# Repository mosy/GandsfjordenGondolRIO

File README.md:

# Gandsfjorden Gondol RIO
## 17.08.24 Skjema for RIO

## 07.08.24 V2 prototype ankommet

Feil etter IO-sjekk:
1 pinne 39/40 er ikke analog inngang, fikses ved av vi bare trenger 1 AI og en PT1000 inngang PT1000 Kobles mot AI2
2 Mangler elektrolytt kondensator, fungerer fint uten
3 hol til skruer er 3.0. settes til 3.1 i neste versjon. 

## 06.09.23

A simple Remote In Out training modeule to interface 24V industrial signals to a modbus PLC. 

 GandsfjordenGondolRIO

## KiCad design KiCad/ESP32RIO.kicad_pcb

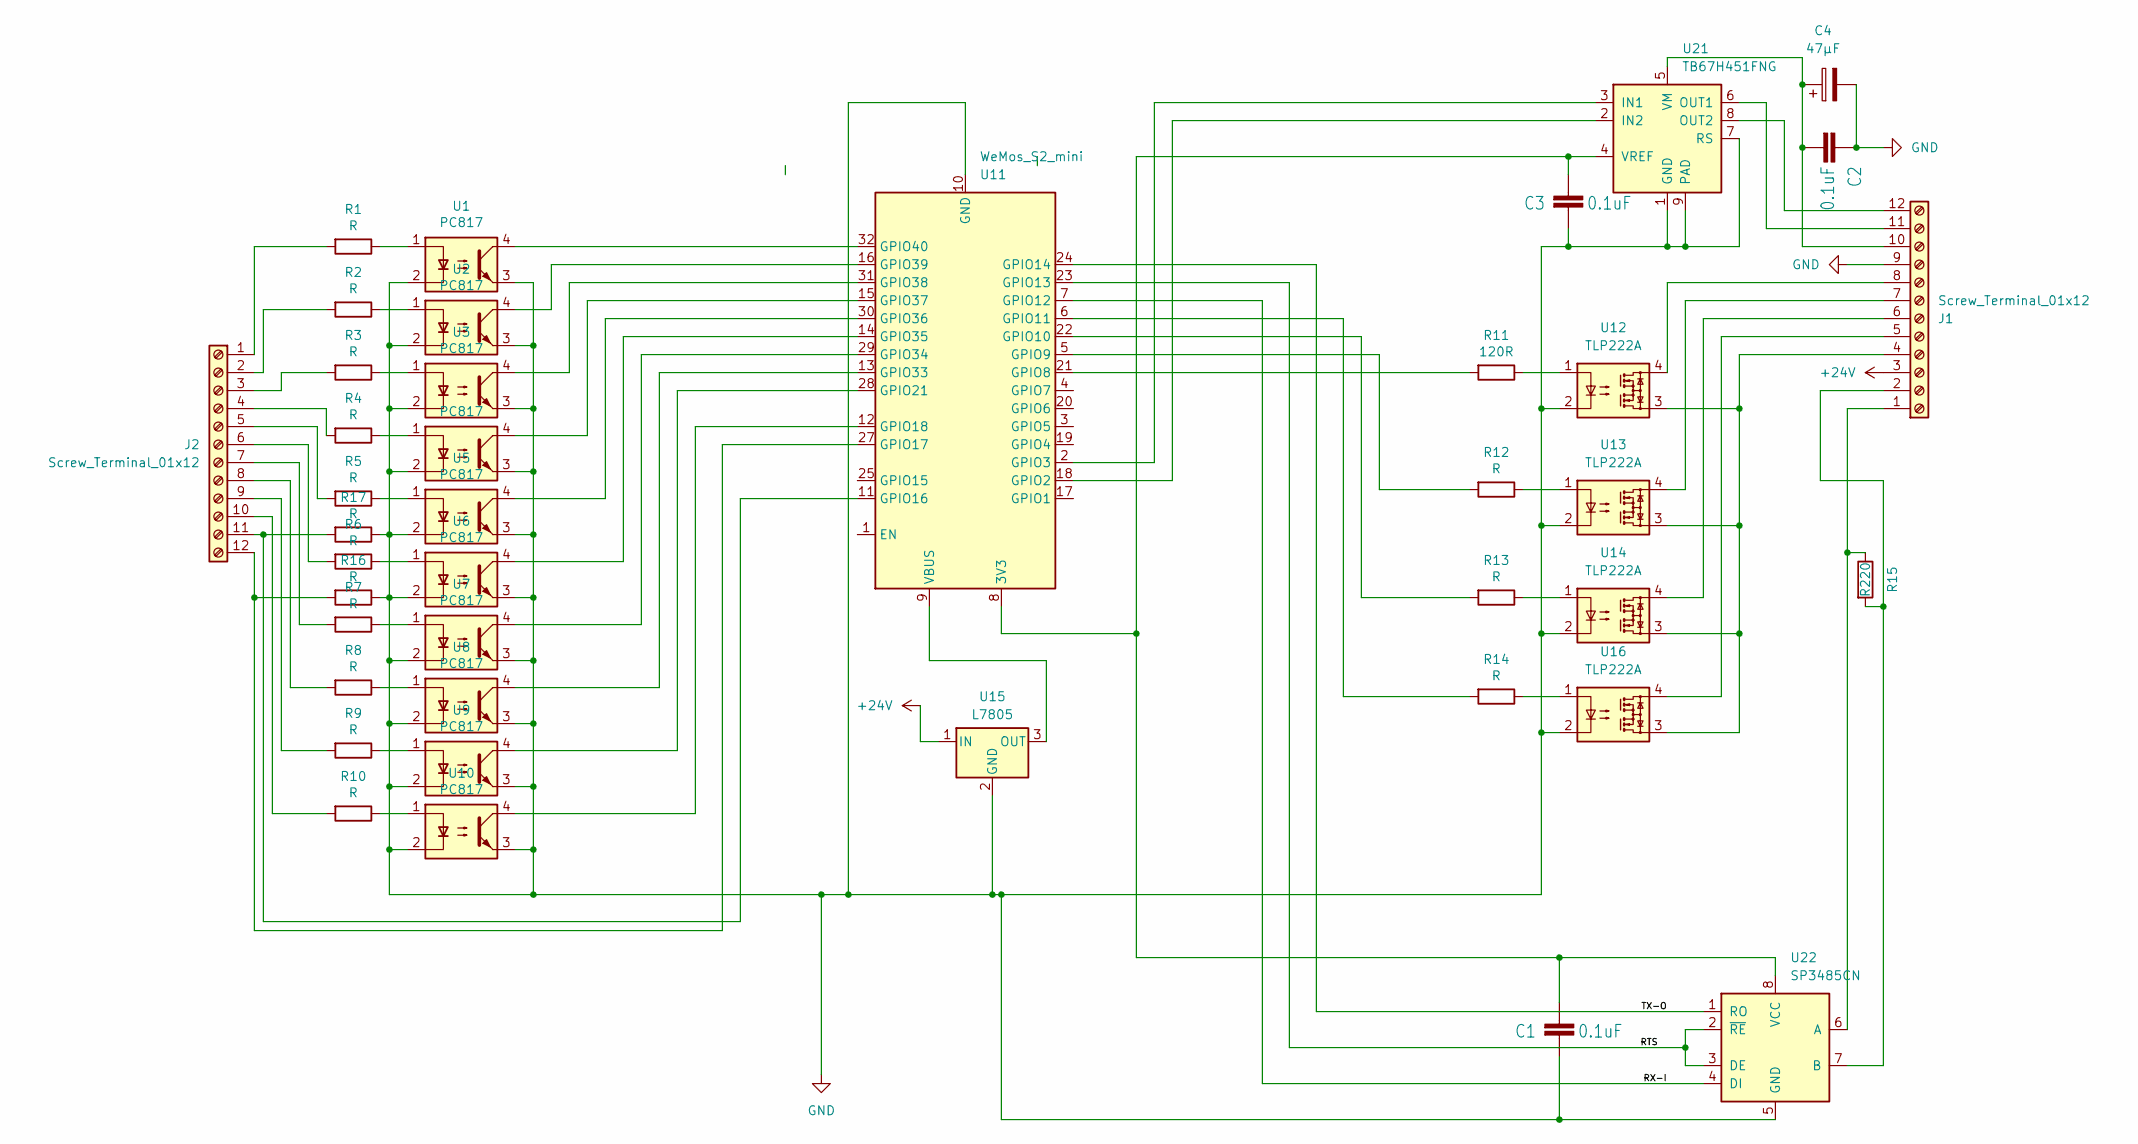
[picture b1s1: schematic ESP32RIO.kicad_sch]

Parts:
C1, C2, C3: 0.1uF; C_1206_3216Metric_Pad1.33x1.80mm_HandSolder
C4: 47µF; CP_Radial_D5.0mm_P2.50mm
J1, J2: Screw_Terminal_01x12; TerminalBlock_Phoenix_MKDS-1,5-12_1x12_P5.00mm_Horizontal
R1, R2, R3, R4, R5, R6, R7, R8, R9, R10, R12, R13, R14, R16, R17: R; R_Axial_DIN0204_L3.6mm_D1.6mm_P2.54mm_Vertical
R11: 120R; R_Axial_DIN0204_L3.6mm_D1.6mm_P2.54mm_Vertical
R15: R220; R_Axial_DIN0204_L3.6mm_D1.6mm_P2.54mm_Vertical
U1, U2, U3, U4, U5, U6, U7, U8, U9, U10: PC817; DIP-4_W7.62mm
U11: WeMos_S2_mini; WEMOS_S2_mini
U12, U13, U14, U16: TLP222A; DIP-4_W7.62mm
U15: L7805; TO-252-2
U21: TB67H451FNG; SOIC-8-1EP_3.9x4.9mm_P1.27mm_EP2.41x3.3mm
U22: SP3485CN; SOIC-8_3.9x4.9mm_P1.27mm

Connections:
+24V: J1.3, U15.1 (IN)
/RTS: U11.23 (GPIO13), U22.2 (~RE), U22.3 (DE)
/RX-I: U11.7 (GPIO12), U22.4 (DI)
/TX-O: U11.24 (GPIO14), U22.1 (RO)
GND: C1.2, C2.1, C3.2, C4.2, J1.9, R16.1, R17.1, U1.2, U1.3, U2.2, U2.3, U3.2, U3.3, U4.2, U4.3, U5.2, U5.3, U6.2, U6.3, U7.2, U7.3, U8.2, U8.3, U9.2, U9.3, U10.2, U10.3, U11.10 (GND), U11.26 (GND), U12.2, U13.2, U14.2, U15.2 (GND), U16.2, U21.1 (GND), U21.7 (RS), U21.9 (PAD), U22.5 (GND)
unnamed: J1.1, R15.1, U22.6 (A)
unnamed: J1.2, R15.2, U22.7 (B)
unnamed: J1.4, U12.3, U13.3, U14.3, U16.3
unnamed: J1.5, U16.4
unnamed: J1.6, U14.4
unnamed: J1.7, U13.4
unnamed: J1.8, U12.4
unnamed: C2.2, C4.1, J1.10, U21.5 (VM)
unnamed: J1.11, U21.6 (OUT1)
unnamed: J1.12, U21.8 (OUT2)
unnamed: J2.1, R1.2
unnamed: J2.2, R2.2
unnamed: J2.3, R3.2
unnamed: J2.4, R4.2
unnamed: J2.5, R5.2
unnamed: J2.6, R6.2
unnamed: J2.7, R7.2
unnamed: J2.8, R8.2
unnamed: J2.9, R9.2
unnamed: J2.10, R10.2
unnamed: J2.11, R17.2, U11.11 (GPIO16)
unnamed: J2.12, R16.2, U11.27 (GPIO17)
unnamed: R1.1, U1.1
unnamed: R2.1, U2.1
unnamed: R3.1, U3.1
unnamed: R4.1, U4.1
unnamed: R5.1, U5.1
unnamed: R6.1, U6.1
unnamed: R7.1, U7.1
unnamed: R8.1, U8.1
unnamed: R9.1, U9.1
unnamed: R10.1, U10.1
unnamed: R11.1, U12.1
unnamed: R12.1, U13.1
unnamed: R13.1, U14.1
unnamed: R14.1, U16.1
unnamed: C1.1, C3.1, U11.8 (3V3), U21.4 (VREF), U22.8 (VCC)
unnamed: U11.18 (GPIO2), U21.2 (IN2)
unnamed: U11.2 (GPIO3), U21.3 (IN1)
unnamed: R11.2, U11.21 (GPIO8)
unnamed: R12.2, U11.5 (GPIO9)
unnamed: R13.2, U11.22 (GPIO10)
unnamed: R14.2, U11.6 (GPIO11)
unnamed: U10.4, U11.12 (GPIO18)
unnamed: U9.4, U11.28 (GPIO21)
unnamed: U8.4, U11.13 (GPIO33)
unnamed: U7.4, U11.29 (GPIO34)
unnamed: U6.4, U11.14 (GPIO35)
unnamed: U5.4, U11.30 (GPIO36)
unnamed: U4.4, U11.15 (GPIO37)
unnamed: U3.4, U11.31 (GPIO38)
unnamed: U2.4, U11.16 (GPIO39)
unnamed: U1.4, U11.32 (GPIO40)
unnamed: U11.9 (VBUS), U15.3 (OUT)

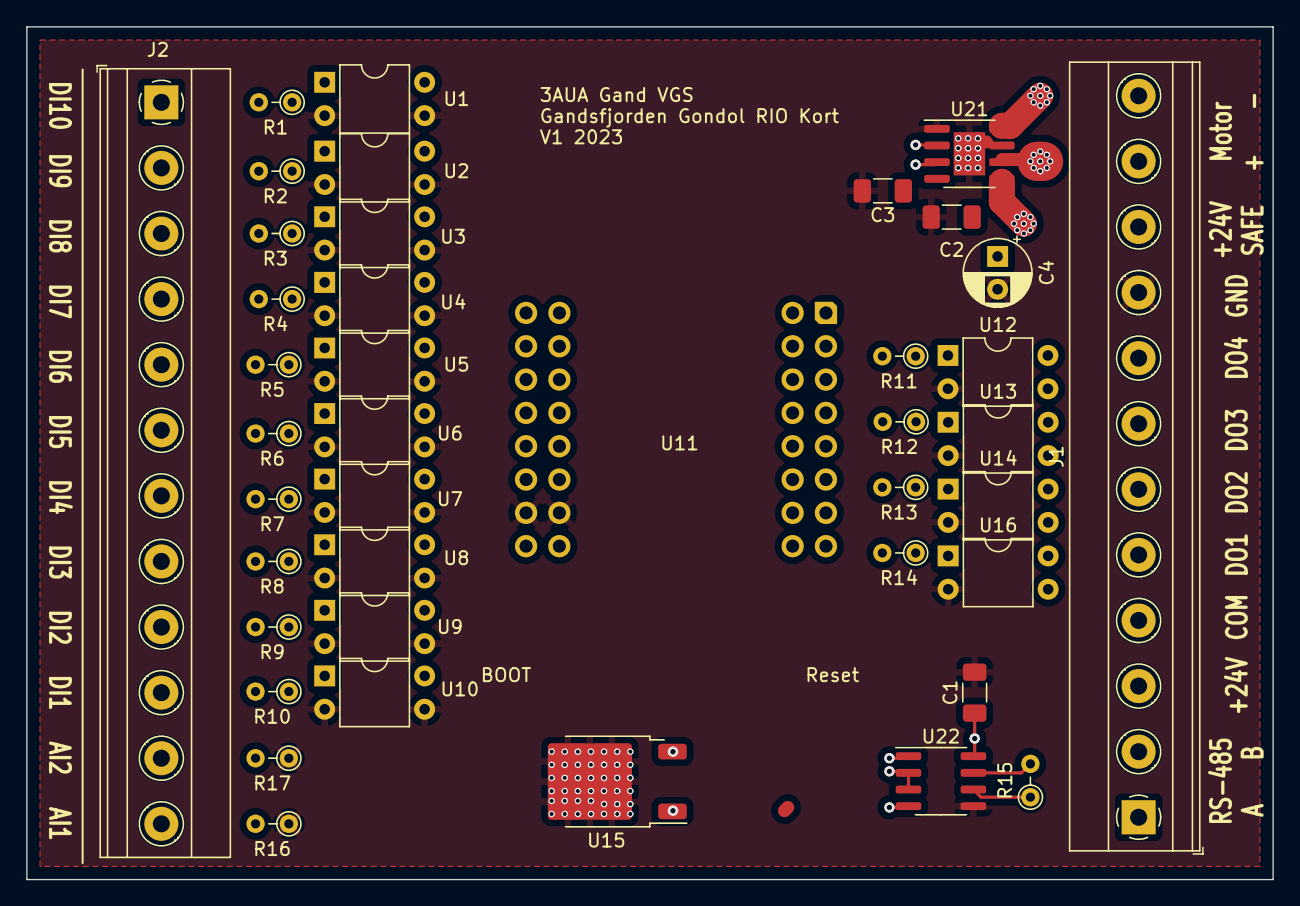
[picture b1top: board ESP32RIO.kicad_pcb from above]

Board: 4 copper layers, 95.0 x 65.0 mm, 41 parts (1 on the bottom side), 59 nets.

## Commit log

2023-03-11 Fungerende modbus med 8DI og 8DO
2023-03-11 Lagt til koblingstegning
2023-03-11 Lagt til koblingstegning svg
2023-03-14 Startet på skjema
2023-03-15 14DI og 2 AI virker
2023-03-15 lagt til bilder
2023-03-17 Lagt til utganger og funnet problemer med 4-20mA ut
2023-07-15 Versjon1
2023-07-15 lagt til bilde av kort
2023-07-15 fix number error in ino file
2023-08-30 v1 sendt til produksjon
2023-08-31 justering
2023-09-04 fix kondensator og regulator
2023-09-06 byttet ut bilder
2024-08-05 v1-finish
2024-08-17 lagt til skjema
2024-08-17 lagt skjeam i README
2024-08-17 forandret tittel i README
2024-08-19 json updage
2024-08-19 oppdatert README
2024-08-19 README again
2024-09-15 hentet frem ino fra V1
2024-09-28 tatt frem gammel firmware
